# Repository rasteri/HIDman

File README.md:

# HIDman
## USB HID to XT / AT / PS/2 / Serial converter

HIDman is an open source device to allow the use of modern USB keyboards and mice on legacy PCs.

Peripherals that support legacy PCs are becoming hard to find, especially for the very first PCs. This project aims to provide a simple cheap solution that will cover everything from the original IBM 5150 PC all the way up to modern computers that have PS/2 ports.

# Features

* (should) Support the majority of standard USB keyboards and mice, including ones that use wireless dongles.
* Also supports (some) USB Game controllers - buttons/axes are mapped to keypresses or mouse actions
* Can emulate the following keyboards :
  * Original IBM PC, XT and clones
  * AT / PS/2
  * Amstrad PC (PC1512, PC1640, PC2xxx, PC3xxx, PC4xxx)
* And the following mice :
  * Serial Mouse (with optional Logitech-style 3rd button)
  * PS/2 Mouse (with optional Intellipoint-style scroll wheel and up to 5 buttons)
* Driverless configuration menu - change settings just by opening a text editor

# How to get one

## Purchase : 

* I have some for sale on my tindie page - https://www.tindie.com/products/rasteri/hidman/
* If you're in the US, retro hack shack also has stock - https://retrohackshack.com/product/hidman-usb-keyboard-converter/

## DIY : 

* Grab an assembled PCB from PCBway : https://www.pcbway.com/project/shareproject/HIDman_USB_to_Retro_PC_Adapter_3b4fb5d5.html
* Also grab the front plate : https://www.pcbway.com/project/shareproject/Front_enclosure_plate_for_HIDman_0aec2ae9.html
* And the rear plate : https://www.pcbway.com/project/shareproject/Rear_Enclosure_for_HIDman_c0ff0b8a.html
* And the enclosure : https://lincolnbinns.com/e-case-a-black-40mm.html
* Don't forget 8x screws : https://lincolnbinns.com/e-case-screws.html (I suggest the thread former ones)
* After assembling the unit, you will need to install firmware. See the "Firmware Update" section below.

# Quickstart Guide

## USB Connection

You can connect many different combinations of USB devices to HIDman.

The most obvious being to connect a keyboard to one USB port, and a mouse to the other one :

Or, you could perhaps connect a wireless keyboard+mouse dongle to one port, and a game controller to the other :

Hub support can be hit-and-miss. This is (mostly) not HIDman's fault - many modern hubs don't support low-speed USB devices properly.

## Newer PCs (PS/2) ###

* Connect male-to-male Mini-DIN cables from HIDman’s keyboard and mouse ports to your PC’s PS/2 ports.
* Turn on your PC.
* If necessary, press HIDman's ⏻ power button to select PS/2 mode (light blue).

## Older PCs (AT/XT and Serial)

* Connect a male-to-male Mini-DIN Cable from HIDman's keyboard port into a Mini-DIN to DIN adapter.
* Connect that adapter to your PC's keyboard port.
* Connect a straight-through male-to-female DE-9 cable from HIDman's serial port to your PC's serial port.
* Turn on your PC.
* Press HIDman's ⏻ power button to select AT mode (light blue), or XT mode (orange) for early 80's IBM PCs and clones.

# Configuration

Configuration is provided through a built-in menu system. No software install is required - all interaction is through the keyboard.

Simply open a text editor on your target PC (eg notepad, edit, vi), then hold HIDman's power button for a few seconds. The menu will be typed out into your text editor.

"Adv.Keyboard" and "Adv.Mouse" switch the keyboard and mouse respectively into "Native Mode". This may be required to access certain functions such as scroll wheels and extra buttons on mice.

**Note : Some USB devices with both keyboard and mouse interfaces (e.g. mice with configurable buttons) require both Adv.Keyboard and Adv.Mouse to be enabled otherwise they behave unpredictably.**

"Intellimouse" enables scroll wheel and 5-button support for PS/2 mice.

"Debug" enables the debug menu. The most useful debugging option is "Dump HID Data". Enabling this dumps information about all USB devices connected after that point. 

If you are having trouble getting a USB device to work, enable HID Dumping then connect the troublesome USB device. Wait for it to finish dumping, then press ESC and save the resulting data to a text file. Then send it to me for analysis.

# Firmware Update

Firmware development is continuing, so if you have problems it's always worth updating to the latest version.

If you're on windows, first install WCH's ISP tool - https://www.wch.cn/downloads/WCHISPTool_Setup_exe.html
If on Mac or Linux, install ch55xtool : https://github.com/MarsTechHAN/ch552tool

The next step is to put the HIDman in firmware update mode.

1. Disconnect everything from HIDman, including all USB devices and PCs. (failure to do this may result in damage to HIDman, your PC, or both).
2. Hold down HIDman's ⏻ power button.
3. Use a USB A-to-A cable to connect HIDman's LOWER USB port to a USB port on your modern PC.

If HIDman doesn't appear in your computers' device list, follow the instructions in the "Debricking" section below.

After that, update instructions will depend on your operating system.

## Windows

Follow the instructions in this diagram :

## Linux or Mac

Pass the -f parameter to ch55xtool specify the firmware file to load. For example :

```
python3 ch55xtool.py -f hidman_axp_v1.1.bin
```

## Debricking

If this is your first time programming HIDman, or you accidentally program a corrupted firmware, you can force it into firmware update mode another way. It can be a bit fiddly though.

1. Disassemble HIDman.
2. Connect the two pads of component C5 (shown above) together using a pair of tweezers or similar.
3. While keeping the pads connected, use a USB A-to-A cable to connect HIDman's LOWER USB port to a USB port on your modern PC.

# Advanced Setups

## Combined PS/2 port
HIDman actually outputs keyboard *and* mouse signals on **BOTH** PS/2 connectors. If you have a PC that can take advantage of this (typically Mini PCs or Laptops), you can keep the cabling neater by using only one cable. **NOTE : You will need to enable "PS2 AUX Output" in the advanced menu.**

Note that there are two different types of Combined PS/2 ports, and HIDman provides for both types. Generally, laptops will need plugged into the Mouse port on HIDman, and Mini PCs want the Keyboard port. If it doesn't work with one port, try the other one.

## Splitter

Another way to take advantage of the Combined PS/2 port functionality is to use a widely-available PS/2 splitter :

This also allows neater cabling, as you could connect both keyboard and mouse ports to the rear, and not have to connect to the front mouse port.

## Technical description

The HIDman is based around the CH559 from WCH, a remarkably flexible chip with **two** USB HOST ports. This makes it ideal for our purposes.

The code is forked from atc1441's excellent repository - https://github.com/atc1441/CH559sdccUSBHost

PCB and enclosure was designed in KiCad - source files are in the hardware directory.

Development is very active but it is usable in its current state.

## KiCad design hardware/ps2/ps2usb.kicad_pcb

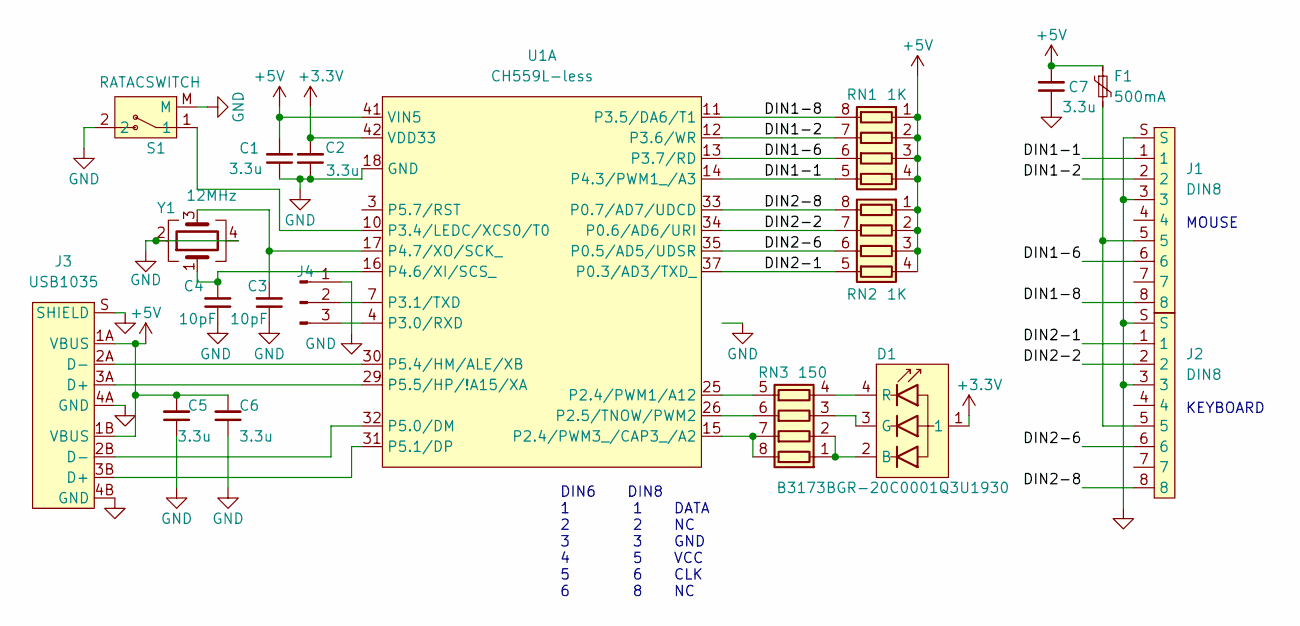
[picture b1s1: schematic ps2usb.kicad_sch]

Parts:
C1, C2, C5, C6, C7: 3.3u; C_0603_1608Metric
C3, C4: 10pF; C_0603_1608Metric
D1: B3173BGR-20C0001Q3U1930
F1: 500mA; Fuse_1206_3216Metric
J1, J2: DIN8
J3: USB1035
J4: Conn_01x03_Pin; PinHeader_1x03_P2.54mm_Vertical
RN1, RN2: 1K; R_Array_Convex_4x0603
RN3: 150; R_Array_Convex_4x0603
S1: RATACSWITCH; TS11
U1: CH559L-less; QFP-12x12_14x14_Pitch0.5mm
Y1: 12MHz; Crystal_SMD_3225-4Pin_3.2x2.5mm

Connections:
+3.3V: C2.2, D1.1, U1.42 (VDD33)
+5V: C1.2, C5.2, C6.2, C7.2, F1.1, J3.1A (VBUS), J3.1B (VBUS), RN1.1 (R1.1), RN1.2 (R2.1), RN1.3 (R3.1), RN1.4 (R4.1), RN2.1 (R1.1), RN2.2 (R2.1), RN2.3 (R3.1), RN2.4 (R4.1), U1.41 (VIN5)
/DIN1-1: J1.1, RN1.5 (R4.2), U1.14 (P4.3/PWM1_/A3)
/DIN1-2: J1.2, RN1.7 (R2.2), U1.12 (P3.6/WR)
/DIN1-6: J1.6, RN1.6 (R3.2), U1.13 (P3.7/RD)
/DIN1-8: J1.8, RN1.8 (R1.2), U1.11 (P3.5/DA6/T1)
/DIN2-1: J2.1, RN2.5 (R4.2), U1.37 (P0.3/AD3/TXD_)
/DIN2-2: J2.2, RN2.7 (R2.2), U1.34 (P0.6/AD6/URI)
/DIN2-6: J2.6, RN2.6 (R3.2), U1.35 (P0.5/AD5/UDSR)
/DIN2-8: J2.8, RN2.8 (R1.2), U1.33 (P0.7/AD7/UDCD)
GND: C1.1, C2.1, C3.1, C4.1, C5.1, C6.1, C7.1, J1.3, J1.S, J2.3, J2.S, J3.4A (GND), J3.4B (GND), J3.S (SHIELD), J4.1, S1.2, S1.M, U1.18 (GND), U1.20 (P4.0/A0/RXD1_), Y1.2, Y1.4
unnamed: D1.2 (B), RN3.1 (R1.1), RN3.2 (R2.1)
unnamed: D1.3 (G), RN3.3 (R3.1)
unnamed: D1.4 (R), RN3.4 (R4.1)
unnamed: F1.2, J1.5, J2.5
unnamed: J4.2, U1.7 (P3.1/TXD)
unnamed: J4.3, U1.4 (P3.0/RXD)
unnamed: RN3.7 (R2.2), RN3.8 (R1.2), U1.15 (P2.4/PWM3_/CAP3_/A2)
unnamed: RN3.6 (R3.2), U1.26 (P2.5/TNOW/PWM2)
unnamed: RN3.5 (R4.2), U1.25 (P2.4/PWM1/A12)
unnamed: S1.1, U1.10 (P3.4/LEDC/XCS0/T0)
unnamed: C4.2, U1.16 (P4.6/XI/SCS_), Y1.1
unnamed: C3.2, U1.17 (P4.7/XO/SCK_), Y1.3
unnamed: J3.2B (D-), U1.32 (P5.0/DM)
unnamed: J3.3B (D+), U1.31 (P5.1/DP)
unnamed: J3.2A (D-), U1.30 (P5.4/HM/ALE/XB)
unnamed: J3.3A (D+), U1.29 (P5.5/HP/!A15/XA)

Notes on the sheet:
DIN6 DIN8 1 1 DATA 2 2 NC 3 3 GND 4 5 VCC 5 6 CLK 6 8 NC
MOUSE
KEYBOARD

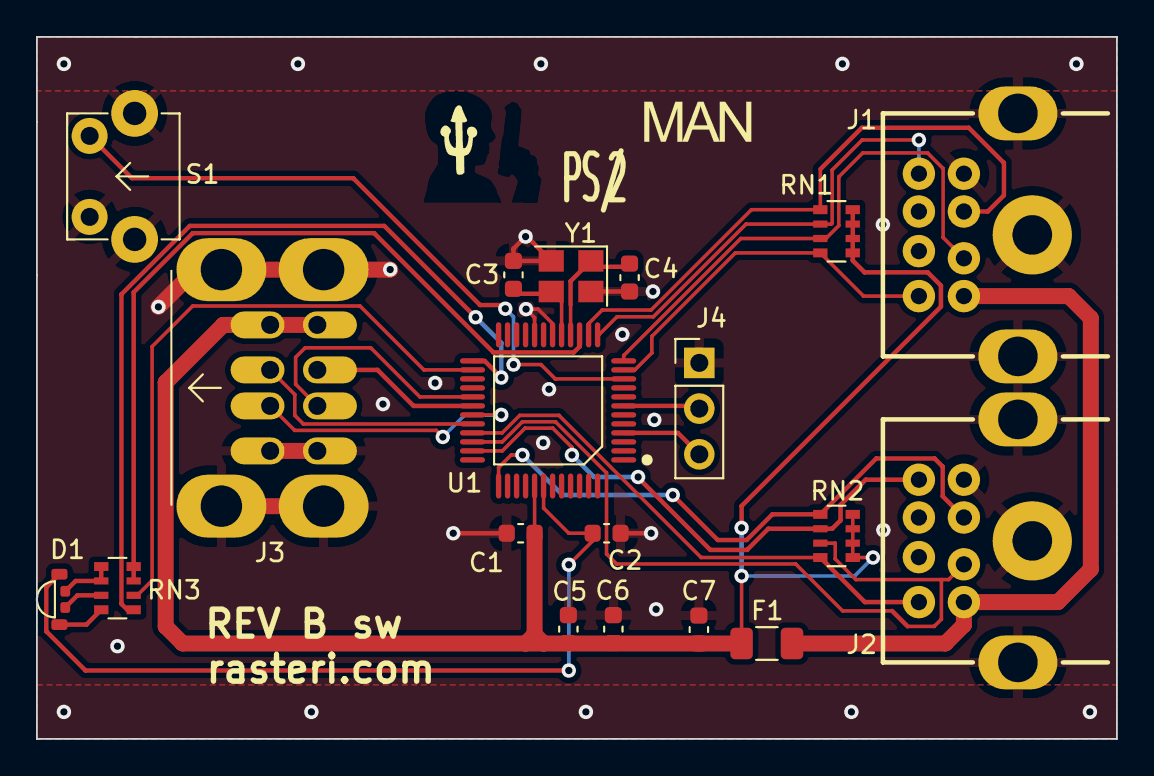
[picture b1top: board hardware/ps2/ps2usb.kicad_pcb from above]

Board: 2 copper layers, 60.0 x 39.0 mm, 19 parts (0 on the bottom side), 27 nets.

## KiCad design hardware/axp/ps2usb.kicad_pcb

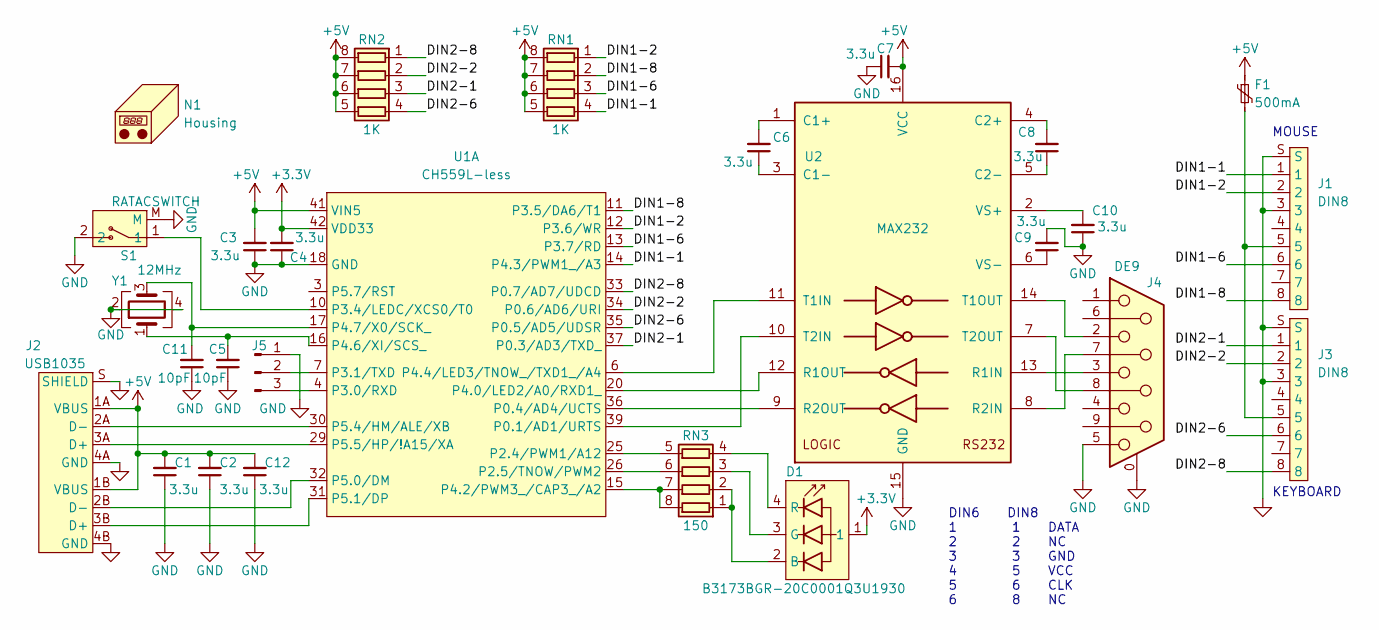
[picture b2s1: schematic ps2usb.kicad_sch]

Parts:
C1, C2, C3, C4, C6, C7, C8, C9, C10, C12: 3.3u; C_0603_1608Metric
C5, C11: 10pF; C_0603_1608Metric
D1: B3173BGR-20C0001Q3U1930
F1: 500mA; Fuse_1206_3216Metric
J1, J3: DIN8
J2: USB1035
J4: DE9; DSUB-9_Female_Horizontal_P2.77x2.84mm_EdgePinOffset7.70mm_H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
J5: Conn_01x03_Pin; PinHeader_1x03_P2.54mm_Vertical
N1: Housing; Enclosure
RN1, RN2: 1K; R_Array_Convex_4x0603
RN3: 150; R_Array_Convex_4x0603
S1: RATACSWITCH; TS11
U1: CH559L-less; QFP-12x12_14x14_Pitch0.5mm
U2: MAX232; SOIC-16_3.9x9.9mm_P1.27mm
Y1: 12MHz; Crystal_SMD_3225-4Pin_3.2x2.5mm

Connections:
+3.3V: C4.2, D1.1, U1.42 (VDD33)
+5V: C1.2, C2.2, C3.2, C7.2, C12.2, F1.1, J2.1A (VBUS), J2.1B (VBUS), RN1.5 (R4.2), RN1.6 (R3.2), RN1.7 (R2.2), RN1.8 (R1.2), RN2.5 (R4.2), RN2.6 (R3.2), RN2.7 (R2.2), RN2.8 (R1.2), U1.41 (VIN5), U2.16 (VCC)
/DIN1-1: J1.1, RN1.4 (R4.1), U1.14 (P4.3/PWM1_/A3)
/DIN1-2: J1.2, RN1.1 (R1.1), U1.12 (P3.6/WR)
/DIN1-6: J1.6, RN1.3 (R3.1), U1.13 (P3.7/RD)
/DIN1-8: J1.8, RN1.2 (R2.1), U1.11 (P3.5/DA6/T1)
/DIN2-1: J3.1, RN2.3 (R3.1), U1.37 (P0.3/AD3/TXD_)
/DIN2-2: J3.2, RN2.2 (R2.1), U1.34 (P0.6/AD6/URI)
/DIN2-6: J3.6, RN2.4 (R4.1), U1.35 (P0.5/AD5/UDSR)
/DIN2-8: J3.8, RN2.1 (R1.1), U1.33 (P0.7/AD7/UDCD)
GND: C1.1, C2.1, C3.1, C4.1, C5.1, C7.1, C9.2, C10.1, C11.1, C12.1, J1.3, J1.S, J2.4A (GND), J2.4B (GND), J2.S (SHIELD), J3.3, J3.S, J4.0 (PAD), J4.5, J5.1, S1.2, S1.M, U1.18 (GND), U2.15 (GND), Y1.2, Y1.4
unnamed: D1.2 (B), RN3.1 (R1.1), RN3.2 (R2.1)
unnamed: D1.3 (G), RN3.3 (R3.1)
unnamed: D1.4 (R), RN3.4 (R4.1)
unnamed: F1.2, J1.5, J3.5
unnamed: J5.2, U1.7 (P3.1/TXD)
unnamed: J5.3, U1.4 (P3.0/RXD)
unnamed: RN3.7 (R2.2), RN3.8 (R1.2), U1.15 (P4.2/PWM3_/CAP3_/A2)
unnamed: RN3.6 (R3.2), U1.26 (P2.5/TNOW/PWM2)
unnamed: RN3.5 (R4.2), U1.25 (P2.4/PWM1/A12)
unnamed: U1.39 (P0.1/AD1/URTS), U2.10 (T2IN)
unnamed: U1.36 (P0.4/AD4/UCTS), U2.9 (R2OUT)
unnamed: S1.1, U1.10 (P3.4/LEDC/XCS0/T0)
unnamed: U1.20 (P4.0/LED2/A0/RXD1_), U2.12 (R1OUT)
unnamed: U1.6 (P4.4/LED3/TNOW_/TXD1_/A4), U2.11 (T1IN)
unnamed: C5.2, U1.16 (P4.6/XI/SCS_), Y1.1
unnamed: C11.2, U1.17 (P4.7/X0/SCK_), Y1.3
unnamed: J2.2B (D-), U1.32 (P5.0/DM)
unnamed: J2.3B (D+), U1.31 (P5.1/DP)
unnamed: J2.2A (D-), U1.30 (P5.4/HM/ALE/XB)
unnamed: J2.3A (D+), U1.29 (P5.5/HP/!A15/XA)
unnamed: C6.2, U2.1 (C1+)
unnamed: C6.1, U2.3 (C1-)
unnamed: C8.2, U2.4 (C2+)
unnamed: C8.1, U2.5 (C2-)
unnamed: J4.3, U2.13 (R1IN)
unnamed: J4.7, U2.8 (R2IN)
unnamed: J4.2, U2.14 (T1OUT)
unnamed: J4.8, U2.7 (T2OUT)
unnamed: C10.2, U2.2 (VS+)
unnamed: C9.1, U2.6 (VS-)

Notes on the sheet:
DIN6 DIN8 1 1 DATA 2 2 NC 3 3 GND 4 5 VCC 5 6 CLK 6 8 NC
MOUSE
KEYBOARD

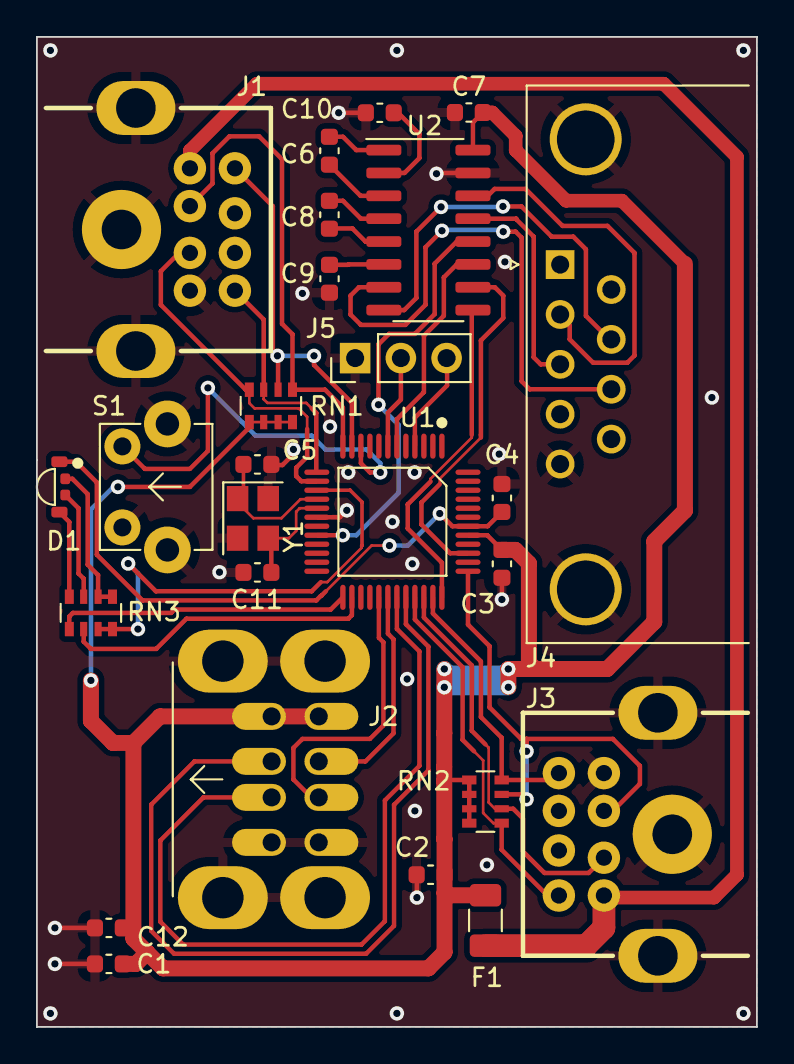
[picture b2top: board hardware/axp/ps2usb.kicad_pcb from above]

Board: 2 copper layers, 40.0 x 55.0 mm, 26 parts (0 on the bottom side), 41 nets.

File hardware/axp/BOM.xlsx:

Item # | Designators | Quantity | Manufacturer | Part no | Desc | Package | Type
1 | C4,C7,C1,C6,C10,C9,C2,C3,C8,C12 | 10 | Samsung | CL10A335KP8NNNC | Cap, 0603, MLCC, 3.3uF, 10v, X5R | SMD 0603 | SMD
2 | C11,C5 | 2 | YAGEO | CC0603JRNPO9BN100 | Cap, 0603, MLCC, 10pF, 50v, C0G | SMD 0603 | SMD
3 | J3,J1 | 2 | HOOYA | DIN-603 | Conn, Mini-DIN, 6pin | Through-Hole | TH
4 | D1 | 1 | TUOZHAN | P4-1204RGBWS2-1.5T-A | LED, RGB, Common Anode | SMD | SMD
5 | RN3 | 1 | YAGEO | YC164-JR-07120RL | Res Array, 4x0603, 120R | SMD 4x0603 | SMD
6 | RN1,RN2 | 2 | YAGEO | YC164-FR-071KL | Res Array, 4x0603, 1K | SMD 4x0603 | SMD
7 | J2 | 1 | SHOU HAN | AF SS-JB17.6 | Conn, USB, 2.0, Type-A, Dual | Through-Hole | TH
8 | U1 | 1 | WCH | CH559L | IC, CH559L | SMD QFP48 | SMD
9 | U2 | 1 | Texas Instruments | MAX232IDR | IC, MAX232 | SMD SOIC16 | SMD
10 | S1 | 1 | Shenzhen Kinghelm Elec | KH-6X6X9H-ZJ | Switch, Tactile, Right Angle, 9mm Actuator Length | Through-Hole | TH
11 | J5 | 1 | DO NOT POPULATE | DO NOT POPULATE | DO NOT POPULATE | DO NOT POPULATE | -
12 | J4 | 1 | XUNPU | D-SUB-DR-9PCM-CB | Conn, D-Sub, DE-9, 9-pin | Through-Hole | TH
13 | F1 | 1 | BHFUSE | BSMD1206-050-30V | 500mA | SMD 1206 | SMD
14 | Y1 | 1 | YXC | X322512MSB4SI | 12MHz | SMD 3225 | SMD

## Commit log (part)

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2022-08-14 code checkin
2022-08-14 input buffer
2022-08-14 Inhibit working
2022-08-15 More keys
2022-08-15 keyboard modifiers, inhibit protocol bugfixes
2022-08-19 schematic entry, test PCB layout
2022-08-20 command replies
2022-08-20 Optimizations
2022-08-20 Mid-cycle data transitions
2022-08-20 mouse command responses
2022-08-21 update PCB
2022-08-21 started messing with joystick
2022-08-21 oops
2022-08-30 Makefile funtimes
2022-09-01 Schematic cleanups
2022-09-01 new pinout
2022-09-03 typematic repeat
2022-09-03 fixed some keyboard protocol bugs
2022-09-04 more PS2 code hanlders
2022-09-05 Mouse chunky buffer
2022-09-11 HID report descriptor parsing
2022-09-14 Proper HID report descriptor parsing
2022-09-15 All devices operate in Report Mode
2022-09-18 Better HID report parsing
2022-09-19 leaky crap
2022-09-22 Joystick mappings
2022-09-24 European keys
2022-09-26 plumbed in ps2 output
2022-10-05 work on serial version enclosure
2022-10-05 bugfix for joypad descriptor
2022-10-23 HID report descriptor memory optimizations
2022-10-27 serial enclosure
2022-10-31 fixed mouse bitfield
2022-11-03 Finished serial enclosure
2022-11-20 LED PWM
2022-11-26 AXP pin assignments
2022-12-11 re enabled menu
2022-12-12 force keyboard/mouse to BOOT protocol
2022-12-22 debug protocol display
2022-12-28 serial packet
2022-12-29 broken
2022-12-30 cleanup
2023-01-08 Serial mouse, LEDs, Boot Mode Debugging
2023-01-09 Case sensitive compilation fixes
2023-01-21 Disable UART0 for HIDman-micro as well
2023-01-23 Check for boot mode before enabling
2023-01-25 Fix serial mouse
2023-01-25 Fix compiler error
2023-01-25 Prepare to support 19200 baud serial mouse
2023-01-25 Make UART word size configurable
2023-01-26 Support 3 mouse buttons
2023-01-26 board outline
2023-01-28 Set U1_FIFO_TRIG properly
2023-01-28 Wired up TXD instead of DTR
2023-02-16 button position change
2023-02-19 reorganized hardware dir
2023-03-07 Fix race with timer interrupt 1 that also modifies PS/2 mouse clock pin 3.7
2023-05-12 added axp bom
2023-07-25 Add missing calls to SelectHubPort
2024-03-22 trivial change
2024-03-24 compilation fixes
2024-03-26 added int size checker, mainly for my own amusement
2024-04-06 Alternate PS/2 pins (for combined mouse/keyboard jacks)
2024-04-06 combined ps2 port bugfix
2024-04-26 XT keyboard support (mostly) working
2024-04-29 Implemented support for PS/2 mouse data reporting enable / disable.
    Data reporting support does fix problem where certain PS/2 controllers will disable
    mouse port on POST if mouse is transmitting anhything while data reporting is off.
    There are also stub functions for implementing scaling / resolution etc, but not
    implemented yet.
2024-05-06 Attempted to add wheel to standard mouse descriptor.
2024-05-06 Support for PS/2 mouse scaling and resolution.
2024-05-06 Wheel scrolling almost works but not there yet... Cannot wrap my head around USB reports etc.
2024-05-06 Improvements to PS/2 mouse resolution support and code quality.
2024-05-06 Support for 5 button intellimouse added.
2024-05-06 menu fix
2024-05-07 Support for original "Hidman PS/2" hardware
2024-05-08 Pictures
2024-05-09 Advanced Mouse/Keyboard mode
2024-05-14 graphic of different hidman setups
2024-05-15 even more hub debug info
2024-05-18 newthing
2024-05-19 Fixed incorrect feature clearing
2024-05-22 one transfer per frame
2024-05-23 fewer bulk transfer initiations per frame
2024-05-28 refactor
2024-05-28 Added crystal to PCB
2024-06-08 redundant code cleanup
2024-06-09 refactoring, soft watchdog
2024-06-11 moved some capacitors around
2024-06-18 Colorblind-safe LED colors
2024-06-18 README
2024-06-18 better images
2024-06-27 setup graphics
2024-06-28 menu pics
2024-07-01 game controller mappings update
2024-07-06 HIDman PS/2 version updated from current AXP
2024-07-07 Cleaned up rogue tracks.
2024-07-07 Clean up of labels and logo.
2024-07-07 Amstrad keyboard initial work
2024-07-08 81 key keyboard support
2024-07-10 simulator working
2024-07-10 split out usb low level stuff
2024-07-11 add presets, fix memory leak
2024-07-15 Split report parser and mapper
2024-07-19 Update ps2usb-BOM.xlsx
    BOM update
2024-07-19 Corrected SMD sizes, updated BOM and placement.
2024-07-24 Updated recommended length of button
    8mm actuator length instead of 9.5mm. JLCPCB part number not updated due to lack of availability.
2024-07-26 more USB refactoring
2024-07-28 updated test harness
2024-07-31 test tweaks, alloc improvements
2024-08-07 Disable sending during USB enumeration
2024-09-02 menu fixes, lots more test data
2024-09-03 Increased max reports
2024-09-09 interfaces allocated from main pool
2024-09-10 Reports and hid segments using linkedlist
2024-09-10 debug disabled
2024-09-26 default HID report bug fixed
2024-09-27 Fix HIDman-mini
2024-09-27 Re-enable menu for HIDman-micro
2024-10-12 hopefully added euro keys to XT
2024-10-12 Hopefully fixed XT enter and dot keys
2024-10-17 keyboard tester
2024-10-17 Keyboard tester work
2024-10-18 massively optimized key tester
2024-10-20 hilarious new name for key tester
2024-10-28 mashpipe workings
2024-11-02 Mashpipe - better key drawing
2024-11-05 unified debug, report mode fixes
2024-11-13 debuggingchanges
2024-11-27 stuff
2024-12-15 data generator
2024-12-18 mashpipe build automation
2024-12-18 BUGS
2024-12-20 hub initialization tweaks
2024-12-25 multi-byte report segments kinda working
2024-12-25 multi-byte report segments working better
2024-12-28 debug info removed
2025-01-06 pokes kinda working
2025-01-19 XT BAT check implemented
2025-02-05 BAT Delay, 5160 compatibility
2025-03-22 Terminal Disabled PS/2 AUX ports by default
    there's an option in the advanced menu to re-enable them
2025-03-25 test funtimes
2025-03-28 parser processing tests
2025-03-29 b4 perf test
2025-03-29 testage
2025-03-30 (mostly) consolidated tests
2025-03-30 reduced mouse latency
2025-04-22 PS/2 BAT tests now sent on startup
2025-04-23 Rate limiting adjustments
2025-04-23 async menu
2025-04-30 Mouse inhibit logic fixes
2025-05-06 Menu Rate Limiter
2025-05-12 version number
2025-05-20 Amstrad ratelimit, memory increase
2025-05-22 Joystick analog stick fix
2025-05-22 Joypad Mouse click button fix
2025-09-11 Added debricking instructions to README
    .
2025-09-11 Added debricking text
2025-09-11 Update image width for C5 in README
    Increased the image width in the README for better visibility.
2025-09-12 automates test
2025-09-12 Test working even better
2025-09-17 12 bit mouse movement tests
2025-09-18 Improve debricking instructions in README
2025-12-09 Media keys mostly working
2025-12-11 red light during init
2026-01-04 Implement nested hub support with recursive enumeration
    - Updated MAX_EXHUB_LEVEL from 1 to 2 to support 2 levels of nested hubs
    - Added hub hierarchy tracking fields to USB_HUB_PORT struct (HubLevel, ParentHub, ParentHubPortIndex, ChildHubPorts)
    - Implemented dynamic allocation/deallocation for child hub ports using andyalloc
    - Created recursive InitializeHubPorts() function to handle nested hub enumeration
    - Updated address allocation to use sequential addressing for better nested hub support
    - Implemented SelectHubPortByDevice() to handle device selection by tracing parent hierarchy
2026-01-04 Add comprehensive documentation for nested hub implementation
    - Created NESTED_HUB_IMPLEMENTATION.md with detailed technical documentation
    - Documents all code changes, design decisions, and implementation details
    - Includes testing information, compilation notes, and future work
    - Provides clear examples and code snippets
    - Documents limitations and backward compatibility
2026-01-04 Fix SDCC pointer type incompatibility errors in SelectHubPortByDevice
    - Changed function parameter from USB_HUB_PORT* to __xdata USB_HUB_PORT* in both declaration and implementation
    - Changed local variables 'current' and 'parent' to use __xdata qualifier
    - Fixes compilation errors: usbll.c:199, usbll.c:224, and usbll.c:209
    - All callers already pass __xdata pointers, so this change makes types consistent
2026-01-05 Fix hub enumeration: remove interface access requirement
    - Removed code that tried to access hub interfaces for status change detection
    - Hub interfaces aren't populated by ParseConfigDescriptor (only HID interfaces are)
    - InitializeHubPorts now enumerates all ports without checking change bitmap
    - This is simpler and doesn't require the status change endpoint
    - Fixed extra closing brace that was causing syntax error
    - Hub enumeration should now work for first-level hubs
2026-01-05 Implement hotplug detection for nested USB hubs
    - Added CheckHubPortChangesRecursive() to detect device attach/detach on all hub ports
    - Recursively checks all hubs (including nested) for port status changes
    - Updated DealUsbPort() to check external hubs every polling cycle
    - When change detected, triggers full re-enumeration via andyclearmem
    - Simple approach: any topology change → clear memory → rescan entire tree
    - Works with nested hubs of any depth within MAX_EXHUB_LEVEL
2026-01-05 Remove external hub polling to eliminate USB transaction overhead
    - Removed CheckHubPortChangesRecursive() function entirely
    - Removed periodic polling of external hub ports from DealUsbPort()
    - Polling all external hub ports required N GetHubPortStatus() calls per hub every 500ms
    - This caused significant performance issues with many USB transactions
    - Now only root hub changes are detected via hardware (QueryHubPortAttach)
    - Users must unplug/replug at root level to trigger re-enumeration for external hub changes
2026-01-05 Implement rotating hub polling with flat list for efficiency
    - Added flat HubList[] array to store pointers to all hubs (max 8)
    - Maintains HubListCount and HubPollIndex for rotating through hubs
    - Poll only ONE hub per cycle instead of all hubs recursively
    - Implemented RebuildHubList() to populate flat list after enumeration
    - AddHubsToListRecursive() traverses tree to find all hubs
    - DealUsbPort() now checks one hub's ports per cycle, rotating to next hub
2026-01-06 Address code review feedback: add constants and improve safety
    - Added HUB_INTERRUPT_TIMEOUT constant (200) for interrupt endpoint timeout
    - Added MAX_HUB_INT_PORTS constant (7) for maximum port bits in interrupt bitmap
    - Fixed potential buffer overflow by checking descLen == 0 explicitly
    - Improved code maintainability with named constants instead of magic numbers
2026-01-06 Fix nested hub enumeration: detect all connected devices
    - Changed port detection logic from requiring BOTH connection status AND change bit to just connection status
    - During initial enumeration, devices already connected may not have change bit set
    - Now checks (hubPortStatus & 0x0001) instead of (hubPortStatus & 0x0001) && (hubPortChange & 0x0001)
    - Clear connection change flag only if it's actually set
    - Fixes issue where second-level hub devices weren't being detected
    - This matches expected USB enumeration behavior for pre-connected devices
2026-01-06 Revert to direct port polling - interrupt endpoints don't work as expected
    - Interrupt endpoints require continuous host polling and just NAK when no data
    - Hubs don't proactively send interrupts without host-initiated polling
    - Reverted to simpler approach: directly check GetHubPortStatus for connection changes
    - Poll all hubs every cycle, checking for connection change bit (0x0001)
    - Much simpler than interrupt endpoint parsing, works reliably
    - Only trigger re-enumeration when actual connection change detected
2026-01-07 Nested Hubs Working!
2026-01-07 more stack optimization
2026-01-07 Round robin change detect scheduler
2026-01-08 LED goes red when enumerating
2026-01-09 Hopefully fixed mouse reset issue
